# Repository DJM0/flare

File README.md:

# Flare 🔥

A high efficiency constant current lighting module for high-powered LEDs.

## V0.2

Based around the [PAM2804](https://www.diodes.com/assets/Datasheets/PAM2804.pdf) 1A step-down LED driver, and [Cree XLamp® XP-E2](https://cree-led.com/media/documents/XLampXPE2.pdf) photo red (650nm) LED. Powered from a USB Type A connector, but can be modified to be powered from a lithium-ion/po battery thanks to the wide range of input voltages supported by the PAM2804 (2.5 to 6.0V).

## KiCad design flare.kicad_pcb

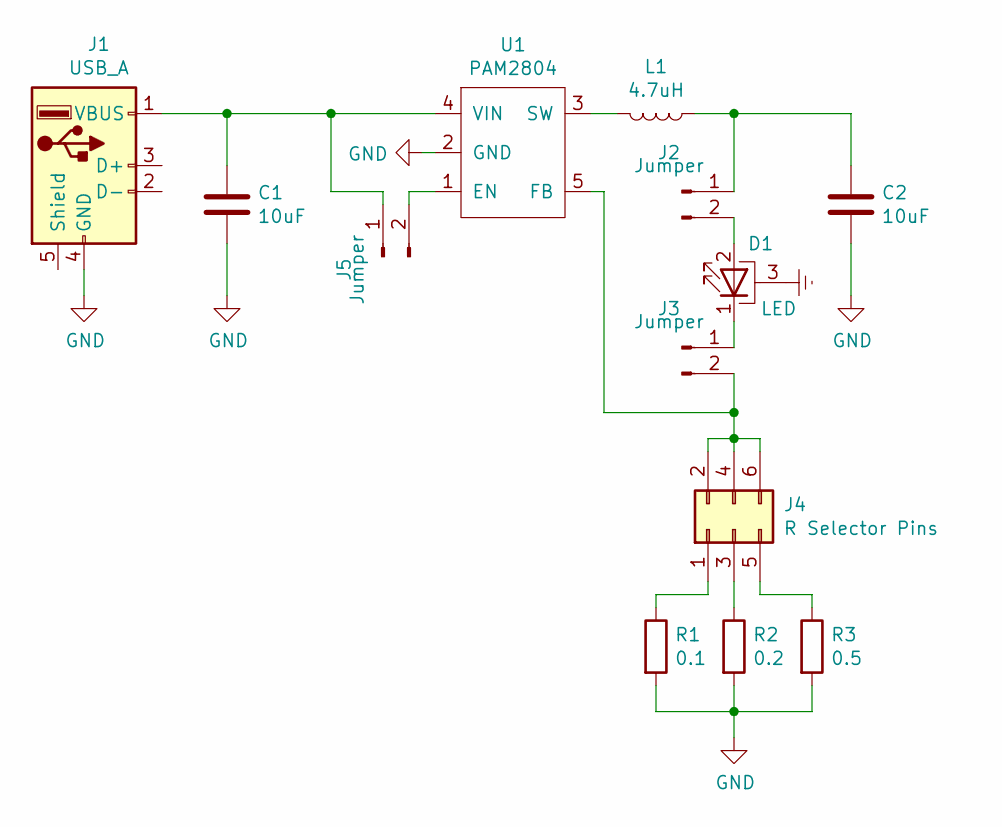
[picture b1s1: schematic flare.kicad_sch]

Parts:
C1, C2: 10uF; C_0805_2012Metric
D1: LED; LED_Cree-XP-G
J1: USB_A; USB_A_CNCTech_1001-011-01101_Horizontal
J2, J3, J5: Jumper; PinHeader_1x02_P2.54mm_Vertical
J4: R Selector Pins; PinHeader_2x03_P2.54mm_Vertical
L1: 4.7uH; L_0805_2012Metric
R1: 0.1; R_1206_3216Metric
R2: 0.2; R_1206_3216Metric
R3: 0.5; R_1206_3216Metric
U1: PAM2804; TSOT-23-5

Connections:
Earth: D1.3 (PAD)
GND: C1.2, C2.2, J1.4 (GND), R1.2, R2.2, R3.2, U1.2 (GND)
unnamed: C1.1, J1.1 (VBUS), J5.1, U1.4 (VIN)
unnamed: C2.1, J2.1, L1.1
unnamed: D1.1 (K), J3.1
unnamed: D1.2 (A), J2.2
unnamed: J3.2, J4.2, J4.4, J4.6, U1.5 (FB)
unnamed: J4.1, R1.1
unnamed: J4.3, R2.1
unnamed: J4.5, R3.1
unnamed: J5.2, U1.1 (EN)
unnamed: L1.2, U1.3 (SW)

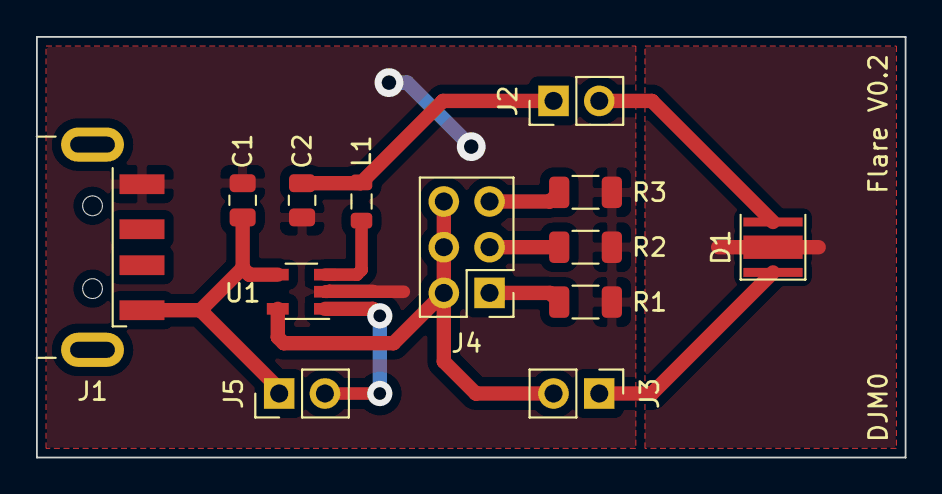
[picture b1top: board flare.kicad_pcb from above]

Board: 2 copper layers, 48.3 x 23.4 mm, 13 parts (0 on the bottom side), 11 nets.

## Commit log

2022-01-08 Flare V0.2
